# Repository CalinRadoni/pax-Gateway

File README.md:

## Usage

To use the library in a project see the `README.md` from the `/examples/QuickStartFiles` directory

## Build and upload

```sh
podman run -it --rm -v /data/platformio:/platformio:Z -v "${PWD}":/project:Z pio run --target clean

podman run -it --rm -v /data/platformio:/platformio:Z -v "${PWD}":/project:Z pio run

# podman run -it --rm -v /data/platformio:/platformio:Z -v "${PWD}":/project:Z --device /dev/ttyUSB0 pio run --target erase

podman run -it --rm -v /data/platformio:/platformio:Z -v "${PWD}":/project:Z --device /dev/ttyUSB0 pio run --target uploadfs

podman run -it --rm -v /data/platformio:/platformio:Z -v "${PWD}":/project:Z --device /dev/ttyUSB0 pio run --target upload

podman run -it --rm -v /data/platformio:/platformio:Z -v "${PWD}":/project:Z --device /dev/ttyUSB0 pio run --target monitor
```

## License

The software and documentation are released under the [GNU GPLv3](http://www.gnu.org/licenses/gpl-3.0.html) License. See the __LICENSE-GPLv3.txt__ file.

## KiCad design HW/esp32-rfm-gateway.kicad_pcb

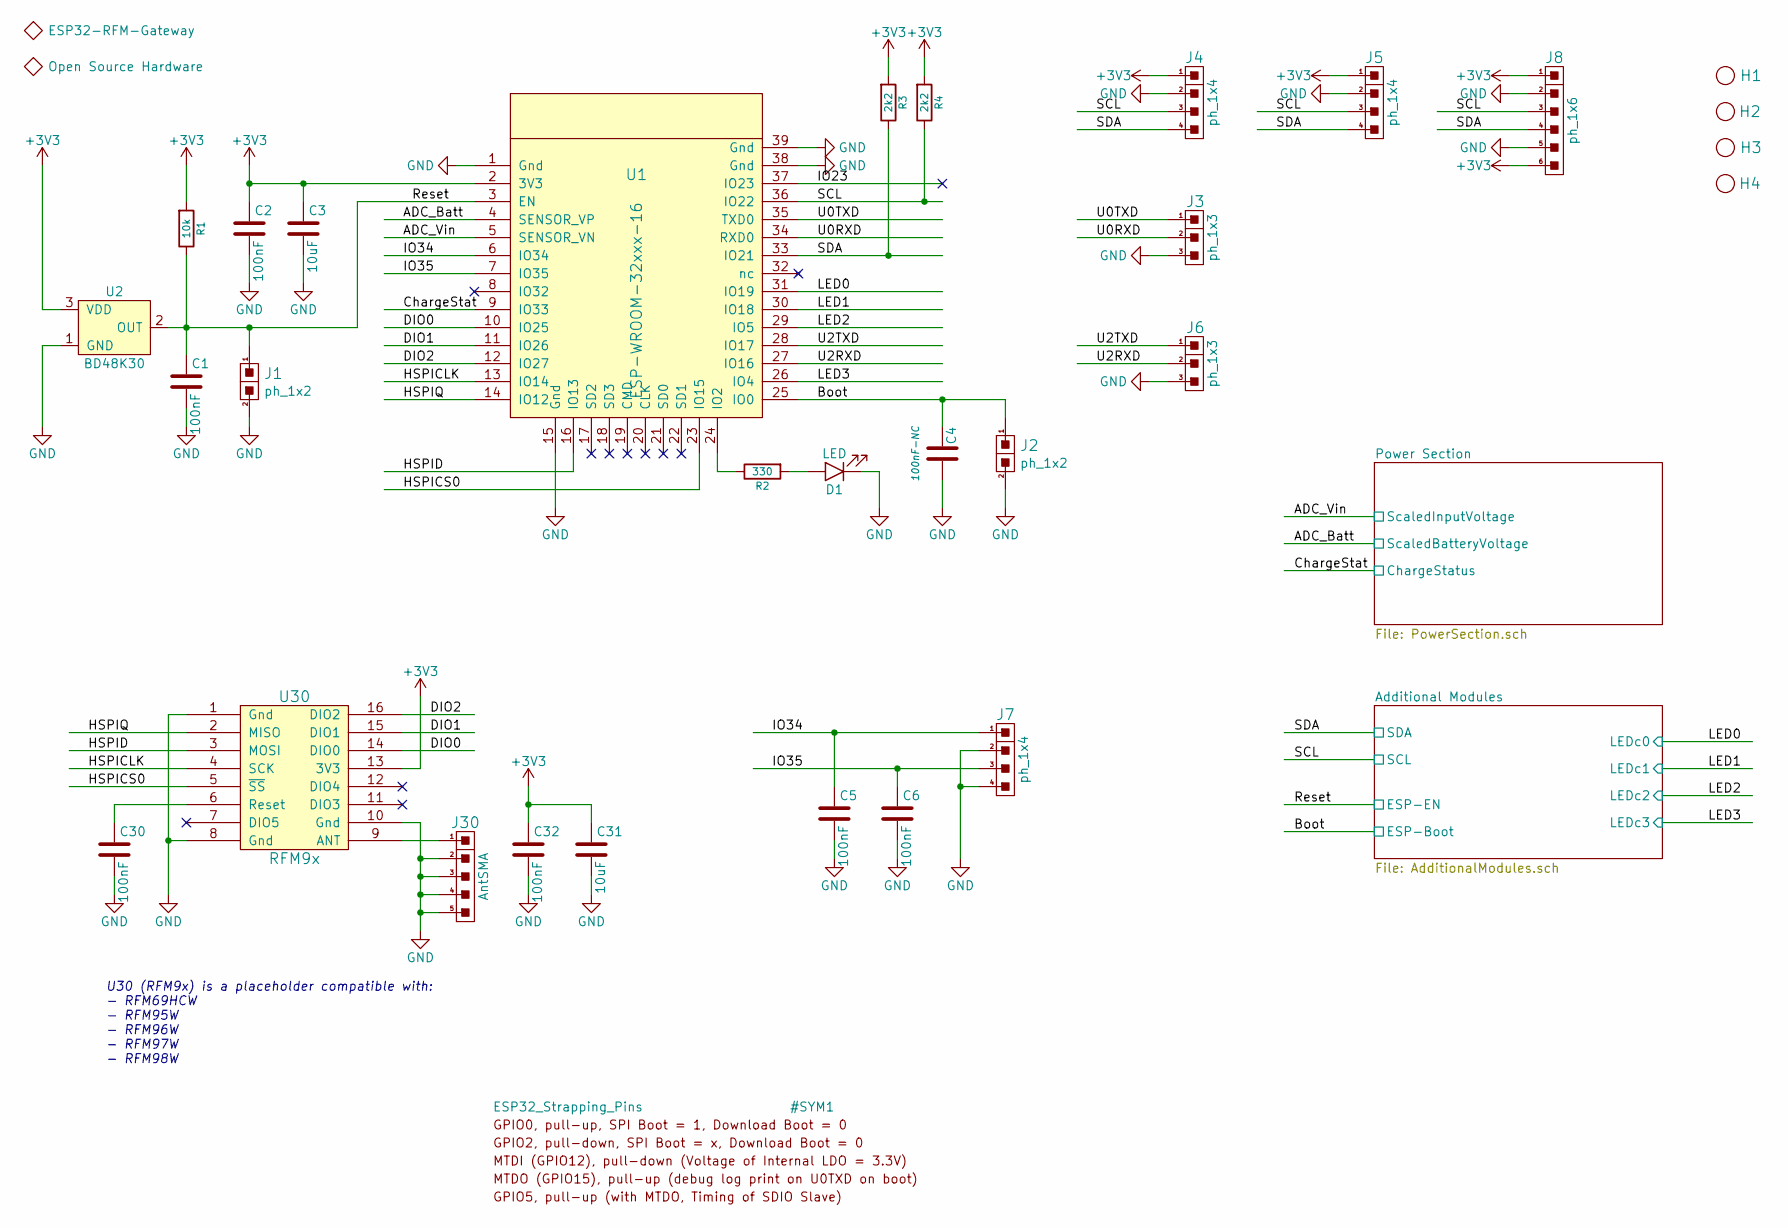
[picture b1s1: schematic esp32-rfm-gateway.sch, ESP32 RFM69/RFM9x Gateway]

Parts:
C1, C2, C5, C6, C30, C32: 100nF; C0805HS; part-number CL21B104KBCNNNC
C3, C31: 10uF; C0805HS; part-number CL21B106KQQNNNE
C4: 100nF-NC; C0805HS; part-number DNP
D1: LED; LED0805HS
H1, H2, H3, H4: Hole; HoleNPT-M2.5
J1, J2: ph_1x2; Pin_Header_Straight_1x02
J3: ph_1x3; Pin_Header_Straight_1x03_Cyan
J4, J5, J7: ph_1x4; Pin_Header_Straight_1x04
J6: ph_1x3; Pin_Header_Straight_1x03_Yellow
J8: ph_1x6; Pin_Header_Straight_1x06; part-number *
J30: AntSMA; SMA-90; part-number RF2-49B-T-00-50-G-HDW
R1: 10k; R0805HS; part-number CRCW080510K0FKEA
R2: 330; R0805HS; part-number CRCW0805330RFKTABC
R3, R4: 2k2; R0805HS; part-number ERJ-6ENF2201V
SYM2: Open Source Hardware; OSHW-Logo_SilkS; part-number DNP
SYM5: ESP32-RFM-Gateway; ValueAsText; part-number DNP
U1: ESP-WROOM-32xxx-16; ESP-WROOM-32-HandSolder; part-number ESP32-WROOM-32D-16
U2: BD48K30; SOT-23-HS; part-number BD48K30G-TL
U30: RFM9x; RFM69HCW; part-number RFM69HCW

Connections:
+3V3: C2.1, C3.1, C31.1, C32.1, J4.1, J5.1, J8.1, J8.6, R1.1, R3.1, R4.1, U1.2 (3V3), U2.3 (VDD), U30.13 (3V3); also elsewhere on the board
/ADC_Batt: U1.4 (SENSOR_VP); also elsewhere on the board
/ADC_Vin: U1.5 (SENSOR_VN); also elsewhere on the board
/Boot: C4.1, J2.1, U1.25 (IO0); also elsewhere on the board
/ChargeStat: U1.9 (IO33); also elsewhere on the board
/DIO0: U1.10 (IO25), U30.14 (DIO0)
/DIO1: U1.11 (IO26), U30.15 (DIO1)
/DIO2: U1.12 (IO27), U30.16 (DIO2)
/HSPICLK: U1.13 (IO14), U30.4 (SCK)
/HSPICS0: U1.23 (IO15), U30.5 (~SS)
/HSPID: U1.16 (IO13), U30.3 (MOSI)
/HSPIQ: U1.14 (IO12), U30.2 (MISO)
/IO34: C5.1, J7.1, U1.6 (IO34)
/IO35: C6.1, J7.3, U1.7 (IO35)
/LED0: U1.31 (IO19); also elsewhere on the board
/LED1: U1.30 (IO18); also elsewhere on the board
/LED2: U1.29 (IO5); also elsewhere on the board
/LED3: U1.26 (IO4); also elsewhere on the board
/Reset: C1.1, J1.1, R1.2, U1.3 (EN), U2.2 (OUT); also elsewhere on the board
/SCL: J4.3, J5.3, J8.3, R4.2, U1.36 (IO22); also elsewhere on the board
/SDA: J4.4, J5.4, J8.4, R3.2, U1.33 (IO21); also elsewhere on the board
/U0RXD: J3.2, U1.34 (RXD0)
/U0TXD: J3.1, U1.35 (TXD0)
/U2RXD: J6.2, U1.27 (IO16)
/U2TXD: J6.1, U1.28 (IO17)
GND: C1.2, C2.2, C3.2, C4.2, C5.2, C6.2, C30.2, C31.2, C32.2, D1.K, J1.2, J2.2, J3.3, J4.2, J5.2, J6.3, J7.2, J7.4, J8.2, J8.5, J30.2, J30.3, J30.4, J30.5, U1.1 (Gnd), U1.15 (Gnd), U1.38 (Gnd), U1.39 (Gnd), U2.1 (GND), U30.1 (Gnd), U30.8 (Gnd), U30.10 (Gnd); also elsewhere on the board
unnamed: C30.1, U30.6 (Reset)
unnamed: D1.A, R2.1
unnamed: J30.1, U30.9 (ANT)
unnamed: R2.2, U1.24 (IO2)

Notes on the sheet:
U30 (RFM9x) is a placeholder compatible with: - RFM69HCW - RFM95W - RFM96W - RFM97W - RFM98W

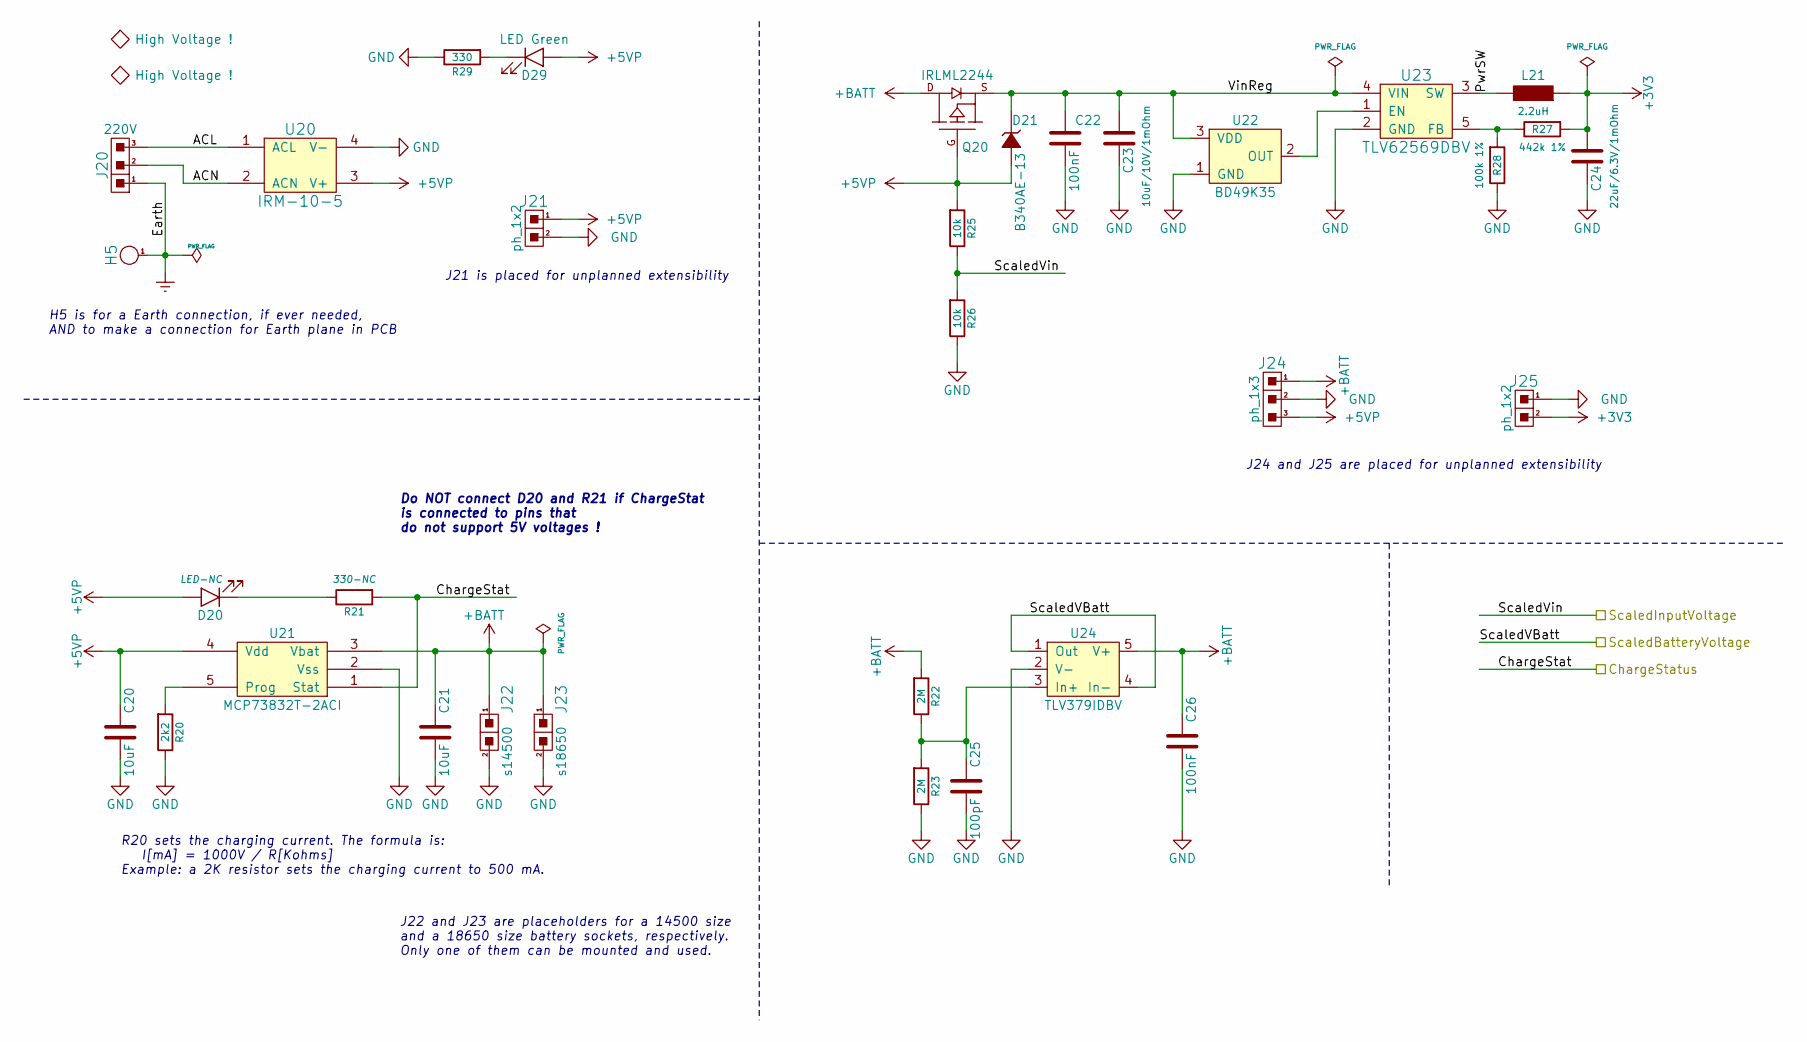
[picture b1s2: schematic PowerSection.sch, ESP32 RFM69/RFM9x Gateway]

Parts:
C20, C21: 10uF; C0805HS; part-number CL21B106KQQNNNE
C22, C26: 100nF; C0805HS; part-number CL21B104KBCNNNC
C23: 10uF/10V/1mOhm; C0805HS; part-number EMK212BJ106KG-T
C24: 22uF/6.3V/1mOhm; C0805HS; part-number JMK212BBJ226MGHT
C25: 100pF; C0805HS; part-number 885012207080
D20: LED-NC; LED0805HS; part-number DNP
D21: B340AE-13; SMA-HS; part-number B340AE-13
D29: LED Green; LED0805HS
H5: HolePlated; SMD_Pins_Big_1x1
J20: 220V~; THT_Pins_Big_1x3
J21: ph_1x2; Pin_Header_Straight_1x02
J22: s14500; BattHolder-AA-PCB
J23: s18650; KEYS-1043; part-number KEYS1043
J24: ph_1x3; Pin_Header_Angled_1x03
J25: ph_1x2; Pin_Header_Angled_1x02
L21: 2.2uH; ASPI-0530HI; part-number ASPI-0530HI-2R2M-T2
Q20: IRLML2244; SOT-23-GSD-HS; part-number IRLML2244TRPbF
R20: 2k2; R0805HS; part-number ERJ-6ENF2201V
R21: 330-NC; R0805HS; part-number DNP
R22, R23: 2M; R0805HS; part-number ERJ-6ENF2004V
R25, R26: 10k; R0805HS; part-number CRCW080510K0FKEA
R27: 442k 1%; R0805HS; part-number ERJ-6ENF4423V
R28: 100k 1%; R0805HS; part-number ERJ-6ENF1003V
R29: 330; R0805HS; part-number CRCW0805330RFKTABC
SYM3, SYM4: High Voltage !; Symbol_HighVoltage_SilkS; part-number DNP
U20: IRM-10-5; IRM222A; part-number IRM-10-5
U21: MCP73832T-2ACI; SOT-23-5-HS; part-number MCP73832T-2ACI
U22: BD49K35; SOT-23-HS; part-number BD49K37G-TL
U23: TLV62569DBV; SOT-23-5-HS; part-number TLV62569DBV
U24: TLV379IDBV; SOT-23-5-HS; part-number TLV379IDBV

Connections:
+3V3: C24.1, J25.2, L21.1, R27.1; also elsewhere on the board
+5VP: C20.1, D20.A, D21.2 (A), D29.A, J21.1, J24.3, Q20.G, R25.1, U20.3 (V+), U21.4 (Vdd)
+BATT: C21.1, C26.1, J22.1, J23.1, J24.1, Q20.D, R22.1, U21.3 (Vbat), U24.5 (V+)
/ADC_Batt: U24.1 (Out), U24.4 (In-); also elsewhere on the board
/ADC_Vin: R25.2, R26.1; also elsewhere on the board
/ChargeStat: R21.1, U21.1 (Stat); also elsewhere on the board
/Power Section/ACL: J20.3, U20.1 (ACL)
/Power Section/ACN: J20.2, U20.2 (ACN)
/Power Section/PwrSW: L21.2, U23.3 (SW)
/Power Section/VinReg: C22.1, C23.1, D21.1 (K), Q20.S, U22.3 (VDD), U23.4 (VIN)
Earth: H5.1, J20.1
GND: C20.2, C21.2, C22.2, C23.2, C24.2, C25.2, C26.2, J21.2, J22.2, J23.2, J24.2, J25.1, R20.2, R23.2, R26.2, R28.2, R29.2, U20.4 (V-), U21.2 (Vss), U22.1 (GND), U23.2 (GND), U24.2 (V-); also elsewhere on the board
unnamed: C25.1, R22.2, R23.1, U24.3 (In+)
unnamed: D20.K, R21.2
unnamed: D29.K, R29.1
unnamed: R20.1, U21.5 (Prog)
unnamed: R27.2, R28.1, U23.5 (FB)
unnamed: U22.2 (OUT), U23.1 (EN)

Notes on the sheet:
J24 and J25 are placed for unplanned extensibility
J21 is placed for unplanned extensibility
R20 sets the charging current. The formula is: I[mA] = 1000V / R[Kohms] Example: a 2K resistor sets the charging current to 500 mA.
J22 and J23 are placeholders for a 14500 size and a 18650 size battery sockets, respectively. Only one of them can be mounted and used.
H5 is for a Earth connection, if ever needed, AND to make a connection for Earth plane in PCB
Do NOT connect D20 and R21 if ChargeStat is connected to pins that do not support 5V voltages !

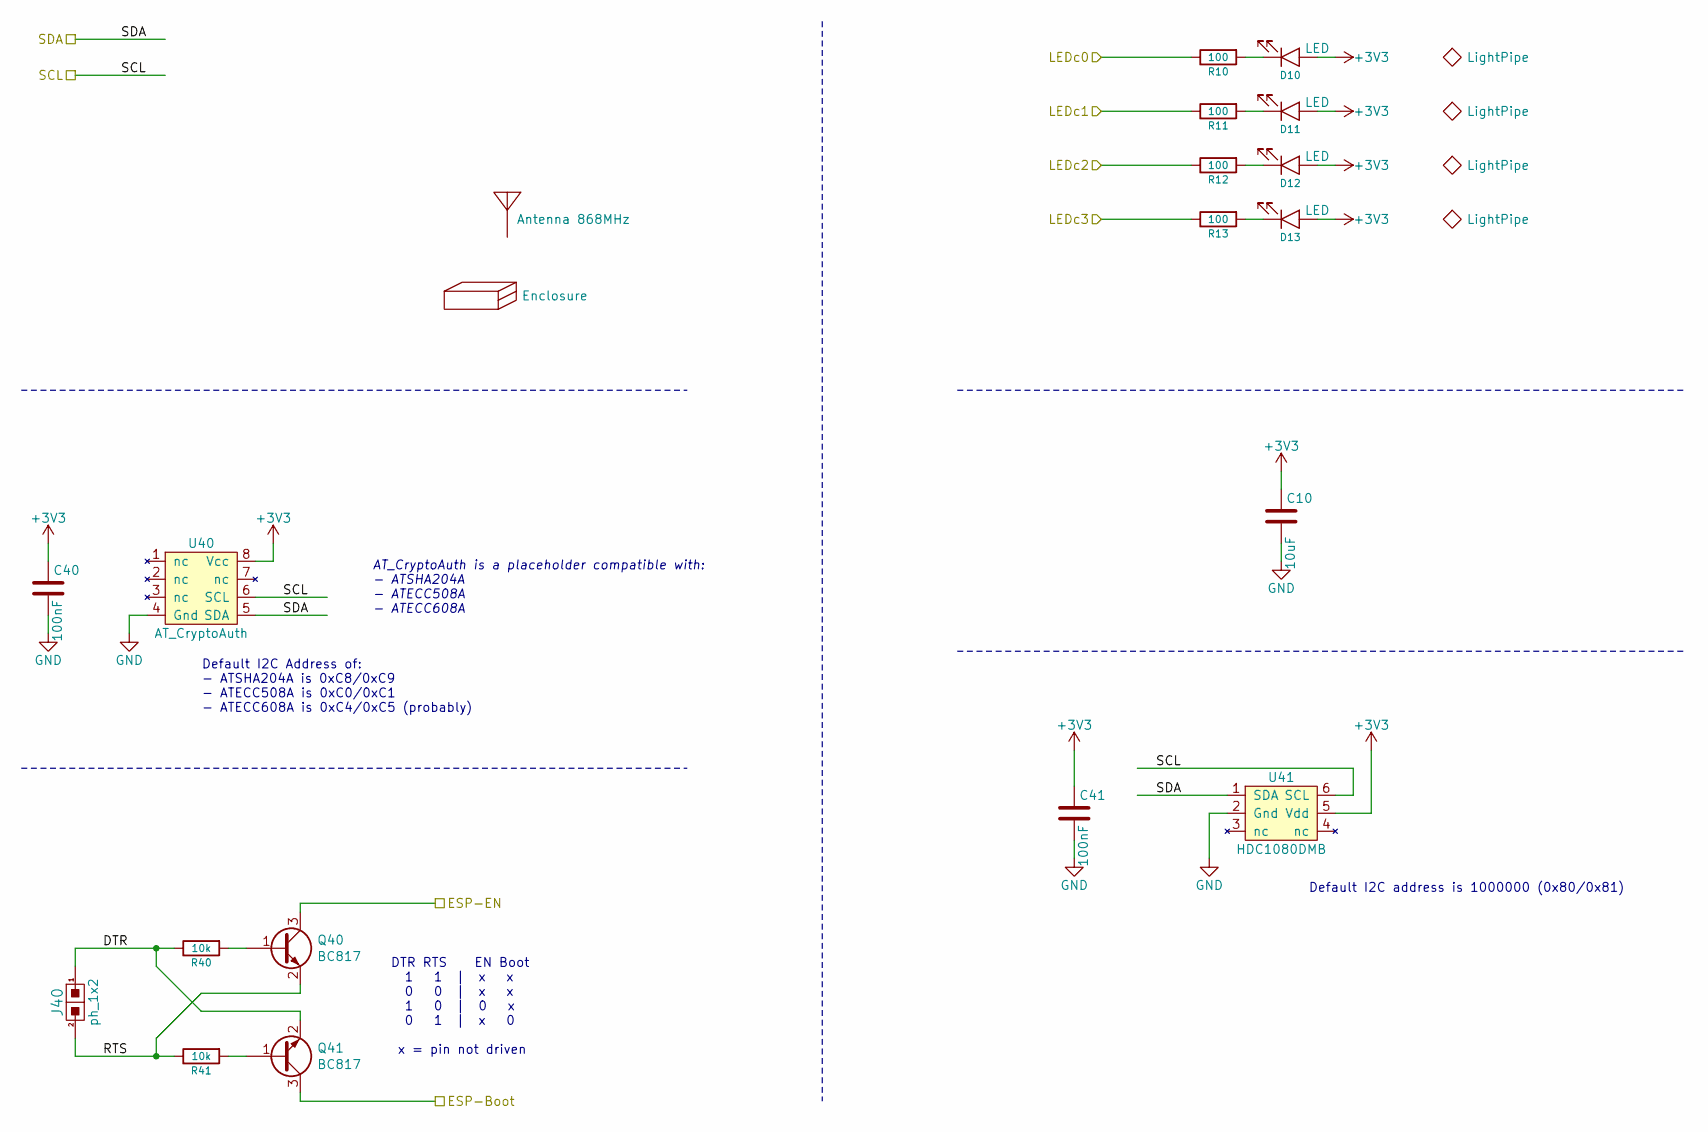
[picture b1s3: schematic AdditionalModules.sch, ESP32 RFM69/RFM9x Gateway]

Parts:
C10: 10uF; C0805HS; part-number CL21B106KQQNNNE
C40, C41: 100nF; C0805HS; part-number CL21B104KBCNNNC
D10, D11, D12, D13: LED; LED0805HS
J40: ph_1x2; Pin_Header_Straight_1x02
Q40, Q41: BC817; SOT-23; part-number BC817-40
R10, R11, R12, R13: 100; R0805HS; part-number ERJ-6ENF1000V
R40, R41: 10k; R0805HS; part-number CRCW080510K0FKEA
SYM6: Antenna 868MHz; VirtualFootprint; part-number 868M-ANT410
SYM9: Enclosure; VirtualFootprint; part-number Gainta G706
SYM10, SYM11, SYM12, SYM13: LightPipe; SLP3-xxx-150-x; part-number SLP3-150-150-F
U40: AT_CryptoAuth; SOIC-8-HS; part-number ATSHA204A/ATECC508A/ATECC608A-SSHDA
U41: HDC1080DMB; WSON6-TI-HDC-HS; part-number HDC1080DMB

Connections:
+3V3: C10.1, C40.1, C41.1, D10.A, D11.A, D12.A, D13.A, U40.8 (Vcc), U41.5 (Vdd); also elsewhere on the board
/Additional Modules/DTR: J40.1, Q41.2 (E), R40.2
/Additional Modules/RTS: J40.2, Q40.2 (E), R41.2
/Boot: Q41.3 (C); also elsewhere on the board
/LED0: R10.2; also elsewhere on the board
/LED1: R11.2; also elsewhere on the board
/LED2: R12.2; also elsewhere on the board
/LED3: R13.2; also elsewhere on the board
/Reset: Q40.3 (C); also elsewhere on the board
/SCL: U40.6 (SCL), U41.6 (SCL); also elsewhere on the board
/SDA: U40.5 (SDA), U41.1 (SDA); also elsewhere on the board
GND: C10.2, C40.2, C41.2, U40.4 (Gnd), U41.2 (Gnd); also elsewhere on the board
unnamed: D10.K, R10.1
unnamed: D11.K, R11.1
unnamed: D12.K, R12.1
unnamed: D13.K, R13.1
unnamed: Q40.1 (B), R40.1
unnamed: Q41.1 (B), R41.1

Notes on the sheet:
AT_CryptoAuth is a placeholder compatible with: - ATSHA204A - ATECC508A - ATECC608A
DTR RTS EN Boot 1 1 | x x 0 0 | x x 1 0 | 0 x 0 1 | x 0 x = pin not driven
Default I2C Address of: - ATSHA204A is 0xC8/0xC9 - ATECC508A is 0xC0/0xC1 - ATECC608A is 0xC4/0xC5 (probably)
Default I2C address is 1000000 (0x80/0x81)

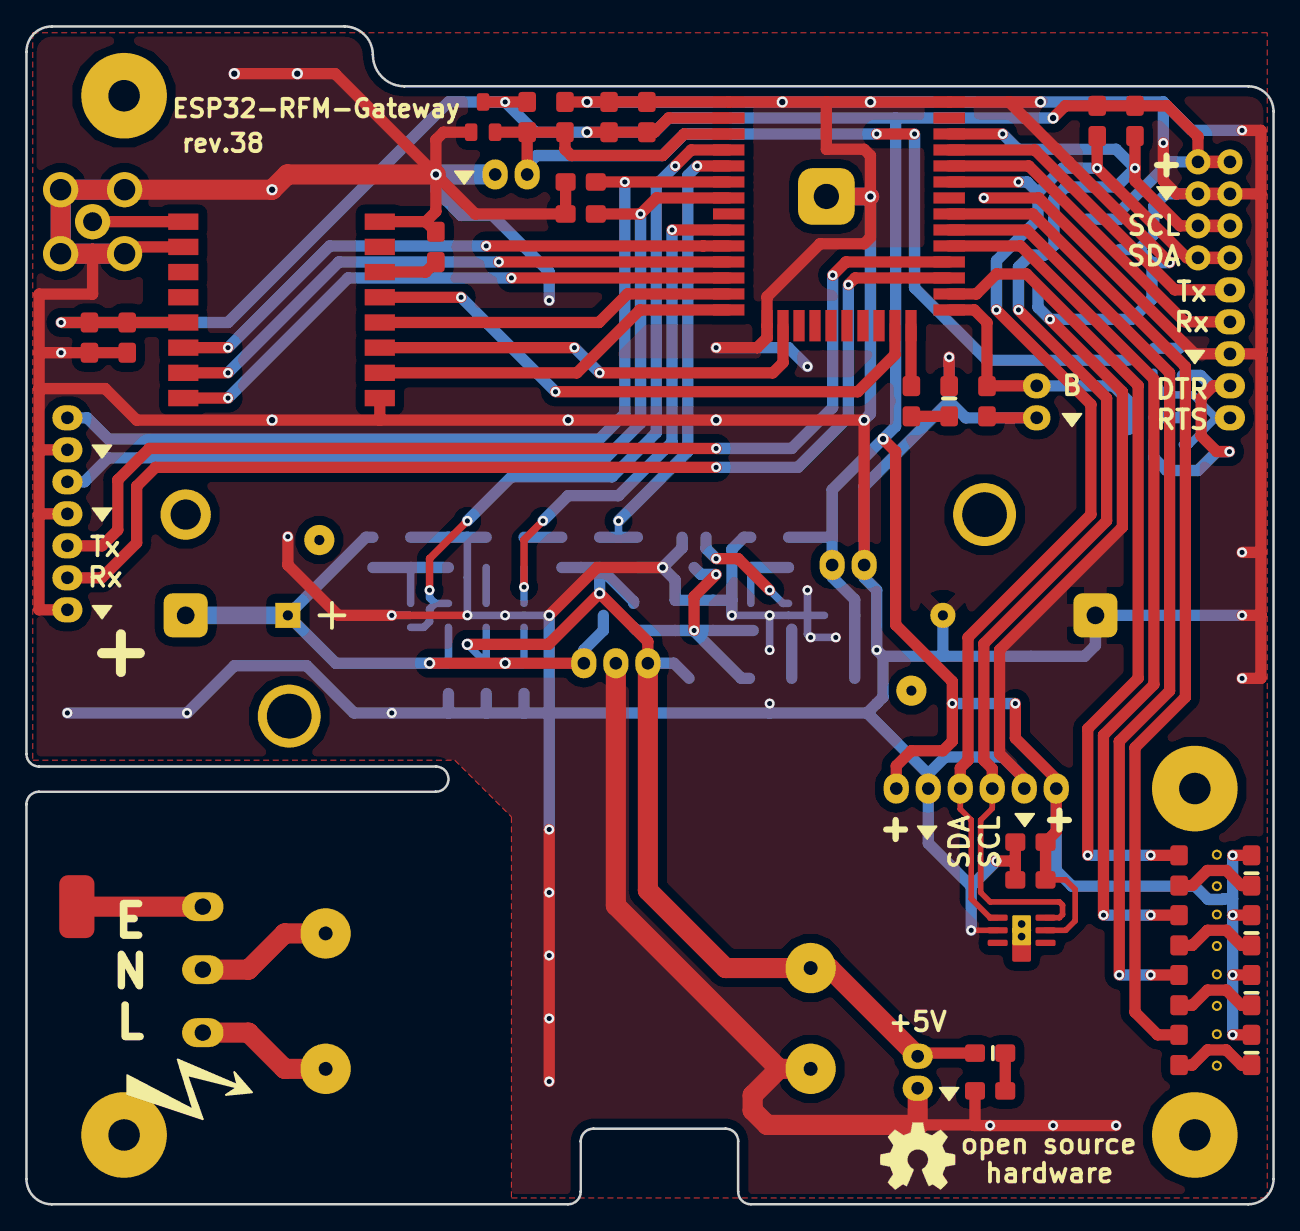
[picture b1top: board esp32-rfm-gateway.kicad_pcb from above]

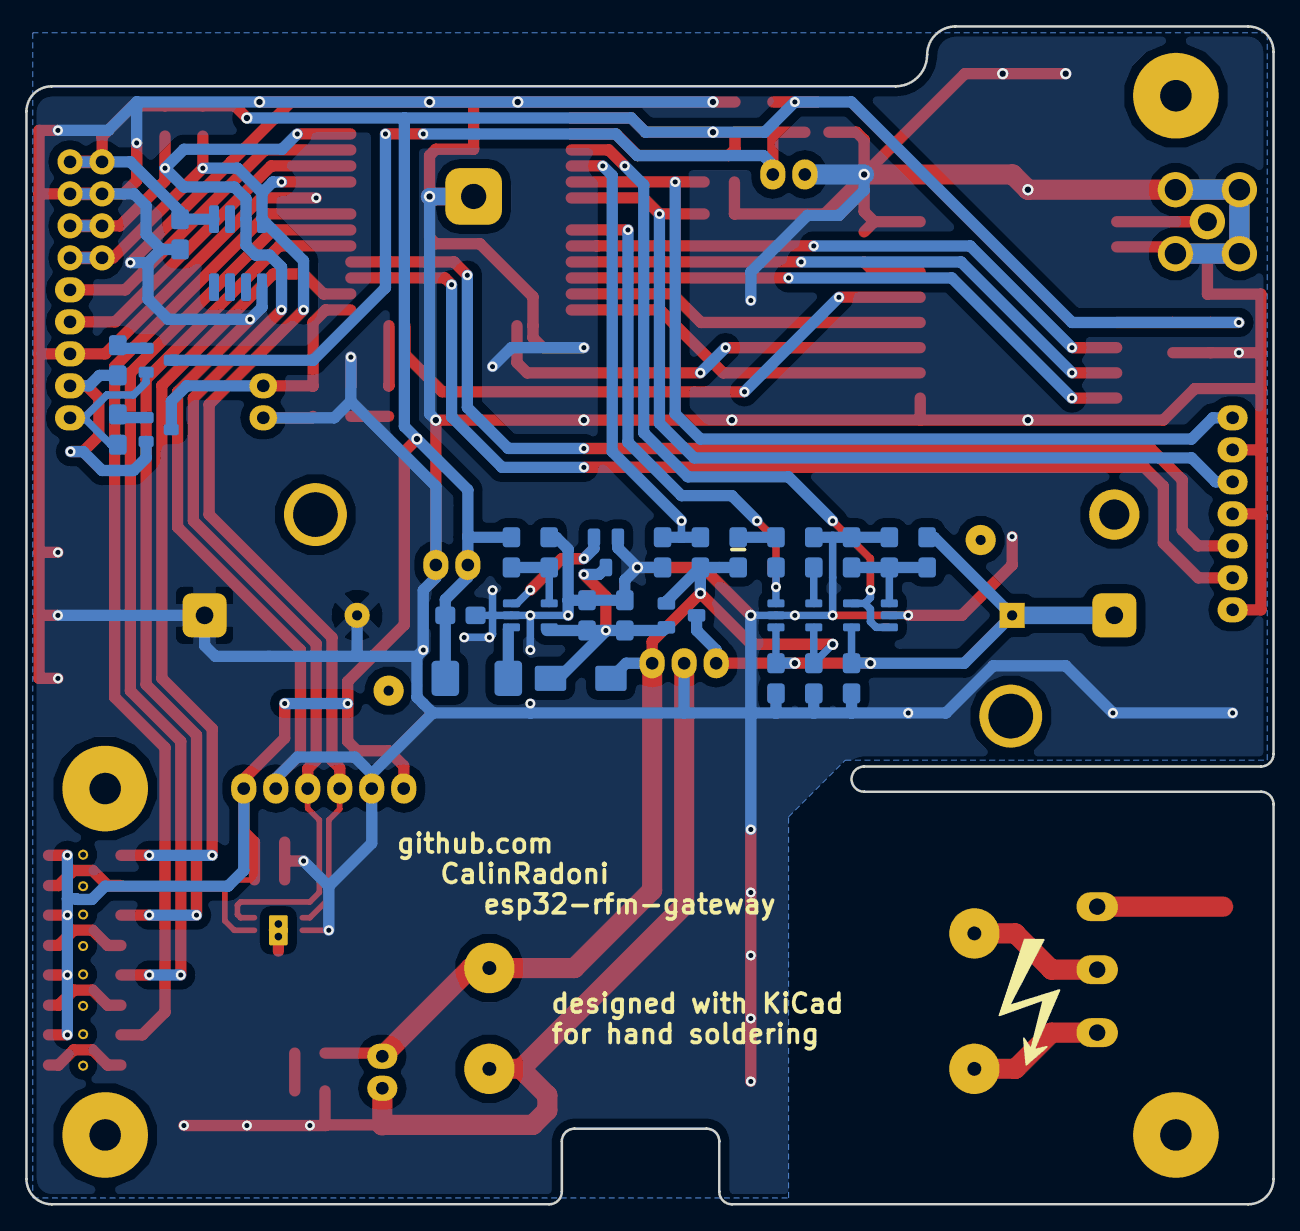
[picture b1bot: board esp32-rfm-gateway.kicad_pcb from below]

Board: 2 copper layers, 99.0 x 93.5 mm, 91 parts (32 on the bottom side), 51 nets.

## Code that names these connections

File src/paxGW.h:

#ifndef paxGW_H
#define paxGW_H

#include <Arduino.h>
#include <SPI.h>

#include "board.h"
#include "paxGWConfig.h"

#ifdef Radio_RFM69
#include <RHReliableDatagram.h>
#include <RH_RF69.h>
#endif

#ifdef SSD1306_DISPLAY
#include "Display_SSD1306.h"
#endif

/*
pax-GW (esp32-rfm-gateway)

ESP-WROOM-32xxx-16 connections
SDA = IO21 (pin 33) with 2k2 pull-up
SCL = IO22 (pin 36) with 2k2 pull-up
SDA and SCL goes to:
- J4, J5, J8
- HDC1080DMB, if installed, address 0x80/0x81
- CryptoAuth chip, if installed
    - ATSHA204A, address 0xC8/0xC9
    - ATECC508A, address 0xC0/0xC1
    - ATECC608A, address 0xC4/0xC5 (probably))

U0RXD and U0TXD = pins 34 and 35 = J3
U0RXD and U0TXD = pins 27 and 28 = J6

LED0 = IO19 (pin 31) with 100 ohms to 3V3
LED1 = IO18 (pin 30) with 100 ohms to 3V3
LED2 = IO5  (pin 29) with 100 ohms to 3V3
LED3 = IO4  (pin 26) with 100 ohms to 3V3

On board LED on IO2 with 330 ohms to ground

HSPICS0 = IO15 (pin 23) = radio -SS
HSPID   = IO13 (pin 16) = radio MOSI
HSPIQ   = IO12 (pin 14) = radio MISO
HSPICLK = IO14 (pin 13) = radio SCK

DIO0 = IO25 (pin 10) = radio DIO0
DIO1 = IO26 (pin 11) = radio DIO1
DIO2 = IO27 (pin 12) = radio DIO2

ChargeStat = IO33 (pin 9) = STAT pin of the MCP73832T-2ACI
ADC_Batt = Sensor_VP (pin 4) = half the battery voltage
ADC_Vin = Sensor_VN (pin 5 ESP-WROOM-32) = half the voltage of the 5V power source

IO34 (pin 6) with 100nF to ground goes to J7
IO35 (pin 7) with 100nF to ground goes to J7
*/

class paxGW_Board : public Board
{
public:
    paxGW_Board(void);
    virtual ~paxGW_Board();

    virtual bool Init_level0(void);
    virtual bool Init_level1(void);
    virtual bool Init_level2(void);
    virtual bool Init_level3(void);

    virtual void CustomReset(void);

    uint16_t GetVIn(void);
    uint16_t GetVBatt(void);
    bool IsCharging(void);

    /**
     * 0 - 3 for LED0 - LED3
     * any other value controls the onboard LED
     */
    void SetLED(uint8_t, bool);

#ifdef SSD1306_DISPLAY
    Display_SSD1306 display;
#endif

    void ShowStatus(void);

#ifdef Radio_RFM69
    RHReliableDatagram *radioManager;
#endif

protected:
    void InitGPIO(void);

    bool InitADC(void);

    SPIClass *hspi;
    bool InitHSPI(void);
    void CleanupHSPI(void);

#ifdef Radio_RFM69
    unsigned char radio_server_address;
    bool CreateRadio(void);
    bool InitializeRadio(void);
    void CleanupRadio(void);
#endif
};

#endif

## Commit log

2020-02-20 Reinitialization after splitting from pax-devices repository
2020-02-22 Adds compile_commands.json and removes useless .vscode form SW directory
2020-03-08 Adds a test page for documentation integrated with GitHub Pages and Jekyll
2021-11-08 Update README.md
    https://forum.kicad.info/t/warning-avoid-all-links-to-kicad-pcb-org-use-kicad-org/31521
2022-02-09 Update VSCode tasks and c_cpp_properties files
2022-02-09 Remove files used for old ESP-IDF based software
2022-02-09 Update gitignores
2022-02-09 Begin of Arduino-based software development
2025-12-30 Migration to ESP32Board library
2025-12-30 KiCad project version update
2025-12-31 Squashed 'lib/RadioHead/' content from commit c286123
    git-subtree-dir: lib/RadioHead
    git-subtree-split: c286123546244e10dad7e764f3a2890453917c29
2025-12-31 Add the UpdateFromWeb library
2025-12-31 Squashed 'lib/RadioHead/' changes from c286123..c8b960a
    c8b960a Solve the warning: '++' expression of 'volatile'-qualified type is deprecated [-Wvolatile]
    git-subtree-dir: lib/RadioHead
    git-subtree-split: c8b960a96deef71483b68f9d09ac2cb7b5e02097
2026-01-01 Squashed 'lib/RadioHead/' changes from c8b960a..830b2b0
    830b2b0 Add Usage information and .gitignore
    acb9158 Remove RH_INTERRUPT_ATTR from member function declarations
    git-subtree-dir: lib/RadioHead
    git-subtree-split: 830b2b033f6822cac6ed9a2d5df967f8cf6e032b
2026-01-01 Added basic support for Monochrome OLEDs based on SSD1306 drivers
2026-01-02 Update Preferences/NVS code
2026-01-03 Added display control functions
2026-02-08 Remove old ES32Board
2026-02-08 Squashed 'lib/ESP32-BoardManager/' content from commit 4ce4ebc
    git-subtree-dir: lib/ESP32-BoardManager
    git-subtree-split: 4ce4ebc6aa99f4b98f319627b9c98a9f08f116c9
2026-02-08 Add the ESP32-BoardManager library
2026-02-09 Use uint32_t for IPv4 addresses
2026-02-09 Get rid of hardcoded WIFI_STA_DEF and WIFI_AP_DEF
    const char *Default_STA_Key = "WIFI_STA_DEF";
    const char *Default_AP_Key = "WIFI_AP_DEF";
    These should have been read from esp-idf implementation but they are not exposed in the public API.
    Current implementation keeps track of default netif(s) and do not uses `ifkey` dependent functions.
2026-02-09 Put the incomplete code for DHCPv4 Captive portal behind a #define
2026-02-09 Squashed 'lib/ESP32-BoardManager/' changes from 4ce4ebc..30d52d2
    30d52d2 Update documentation
    0b1cf77 Put the incomplete code for DHCPv4 Captive portal behind a #define
    b499a9e Get rid of hardcoded WIFI_STA_DEF and WIFI_AP_DEF
    3ca89cb Use uint32_t for IPv4 addresses
    98f2d09 Add the ESP32-BoardManager library
    git-subtree-dir: lib/ESP32-BoardManager
2026-02-16 Working web settings
